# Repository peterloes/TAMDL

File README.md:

# Timed Animal Manipulation Data Logger (TAMDL)
### use timers to trigger your devices

Authors: Loës P., Kempenaers B. (2019) 

Platform for animal observation and manipulation. 

An efficient system to monitor animal behaviour in wildlife
as well as in laboratory settings.

-	Compatible with different RFID systems and triggers
-	Low power consumption and specific data collection lead to long lasting collection periods
-	Applicable world-wide due to its compatibility with different types of radio clock receivers 
-	High observation quality through low disturbance of the animals
- Three user-defined power outputs that can individually be switched on or off at user-defined times

- Time Synchronization with atomic clock once a day to ensure optimal data quality
- Current Control twice a day
- Forecast for Battery-Change implemented
- Energy Bypass so that Date and Time are maintained even when changing battery
- Hyperterminal Output, to get real-time data to the computer/laptop
- Low-Power Device 
- Measure Voltage and Current from your triggered devices 

Picture: Prototype "Activity Logger" with RFID-Reader

https://github.com/peterloes/TAMDL/blob/master/Getting_Started_Tutorial/1_poster_overview_2.pdf

Timed camera trap on nestbox top:

https://github.com/peterloes/TAMDL/blob/master/Getting_Started_Tutorial/1_poster_overview_1.pdf

Raw data on SD Card:

https://github.com/peterloes/TAMDL/blob/master/Getting_Started_Tutorial/6_rawdata_BOX0999.TXT

Configuration data on SD Card:

https://github.com/peterloes/TAMDL/blob/master/Software/CONFIG.TXT

Optional components:

https://github.com/peterloes/Light_Barrier

https://github.com/peterloes/Servo_Engine

https://github.com/peterloes/Linear_Engine

https://github.com/peterloes/Booter_RFID-MS_MOMO_TAMDL

https://github.com/peterloes/Clock_receiver_RFID-MS_MOMO_TAMDL

Manufacture:

https://github.com/peterloes/TAMDL/blob/master/Getting_Started_Tutorial/5_Supplier.txt

C is the Greenest Programming Language

To achieve its power and energy-efficiency features, EFM32 products utilize ultralow active and idle power,
fast wakeup and processing times, and most important, the ability to intelligently interact with peripherals
and sensors autonomously without waking up the CPU and consuming more power.

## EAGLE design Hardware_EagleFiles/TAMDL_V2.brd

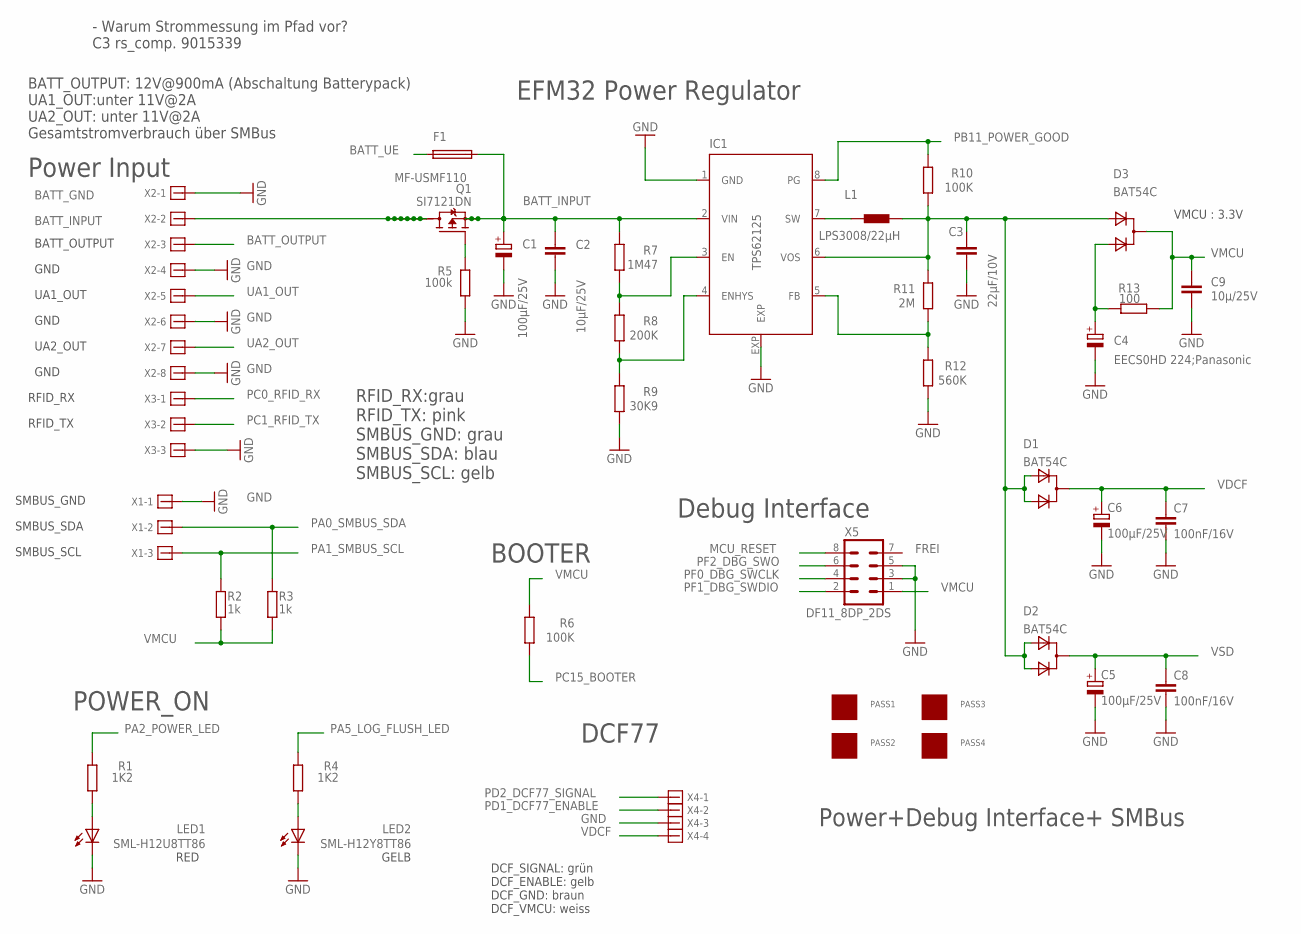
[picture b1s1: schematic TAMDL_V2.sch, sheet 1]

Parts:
C1, C5, C6: 100µF/25V; PANASONIC_E
C2: 10µF/25V; C1206
C3: 22µF/10V; C0603
C4: EECS0HD 224;Panasonic; GOLDCAPSPK-V
C7, C8: 100nF/16V; C0805
C9: 10µ/25V; C1206
D1, D2, D3: BAT54C; SOT-23$1
F1: MF-USMF110; PFUF_1210POLY
IC1: TPS62125; DSG_PWSO-N8_EXP
L1: LPS3008/22µH; LPS3008
LED1: SML-H12U8TT86; CHIPLED_0805
LED2: SML-H12Y8TT86; CHIPLED_0805
PASS1, PASS2, PASS3, PASS4: ROUND_1MM1.5; ROUND2_1.5MM
Q1: SI7121DN; TRANSISTOR-FET_1212-8S
R1, R4: 1K2; R0805
R2, R3: 1k; R0805
R5: 100k; R0805
R6, R10: 100K; R0805
R7: 1M47; R0805
R8: 200K; R0805
R9: 30K9; R0805
R11: 2M; R0805
R12: 560K; R0805
R13: 100; R0805
X1, X3: 1803439
X2: 1803484
X4: 1803442
X5: DF11_8DP_2DS; DP11_8DP-2DS

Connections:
1: C3.1, D1.2 (A1), D1.3 (A2), D2.2 (A1), D2.3 (A2), D3.2 (A1), IC1.6 (VOS), L1.2, R10.1, R11.2
BAT+: Q1.5 (D), Q1.6 (D), Q1.7 (D), Q1.8 (D), Q1.9 (D), Q1.10 (D), Q1.11 (D), X2.2
BATT_INPUT: C1.+, C2.1, F1.P$2 (2), IC1.2 (VIN), Q1.1 (S), Q1.2 (S), Q1.3 (S), R7.2; also elsewhere on the board
BATT_OUTPUT: X2.3; also elsewhere on the board
BATT_UE: F1.P$1 (1); also elsewhere on the board
GND: C1.-, C2.2, C3.2, C4.-, C5.-, C6.-, C7.2, C8.2, C9.1, IC1.1 (GND), IC1.EXP, LED1.C, LED2.C, R5.1, R9.1, R12.1, X1.1, X2.1, X2.4, X2.6, X2.8, X3.3, X4.3, X5.3, X5.5; also elsewhere on the board
MCU_RESET: X5.8; also elsewhere on the board
unnamed: LED1.A, R1.2
unnamed: C4.+, D3.3 (A2), R13.2
unnamed: LED2.A, R4.2
unnamed: IC1.3 (EN), R7.1, R8.2
unnamed: IC1.4 (ENHYS), R8.1, R9.2
unnamed: IC1.7 (SW), L1.1
unnamed: IC1.5 (FB), R11.1, R12.2
unnamed: Q1.4 (G), R5.2
PA0_SMBUS_SDA: R3.2, X1.2; also elsewhere on the board
PA1_SMBUS_SCL: R2.2, X1.3; also elsewhere on the board
PA2_POWER_LED: R1.1; also elsewhere on the board
PA5_LOG_FLUSH_LED: R4.1; also elsewhere on the board
PB11_POWER_GOOD: IC1.8 (PG), R10.2; also elsewhere on the board
PC0_RFID_RX: X3.1; also elsewhere on the board
PC1_RFID_TX: X3.2; also elsewhere on the board
PC15_BOOTER: R6.1; also elsewhere on the board
PD1_DCF77_ENABLE: X4.2; also elsewhere on the board
PD2_DCF77_SIGNAL: X4.1; also elsewhere on the board
PF0_DBG_SWCLK: X5.4; also elsewhere on the board
PF1_DBG_SWDIO: X5.2; also elsewhere on the board
PF2_DBG_SWO: X5.6; also elsewhere on the board
UA1_OUT: X2.5; also elsewhere on the board
UA2_OUT: X2.7; also elsewhere on the board
VDCF: C6.+, C7.1, D1.1 (C), X4.4
VMCU: C9.2, D3.1 (C), R2.1, R3.1, R6.2, R13.1, X5.1; also elsewhere on the board
VSD: C5.+, C8.1, D2.1 (C); also elsewhere on the board

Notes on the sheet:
BATT_GND
BATT_INPUT
BATT_OUTPUT
UA1_OUT
UA2_OUT
GND
RFID_RX
Power+Debug Interface+ SMBus
Power Input
SMBUS_SCL
SMBUS_SDA
SMBUS_GND
EFM32 Power Regulator
Debug Interface
POWER_ON
FREI
VMCU : 3.3V
RED
GELB
BATT_OUTPUT: 12V@900mA (Abschaltung Batterypack) UA1_OUT:unter 11V@2A UA2_OUT: unter 11V@2A Gesamtstromverbrauch über SMBus
RFID_TX
DCF77
RFID_RX:grau RFID_TX: pink SMBUS_GND: grau SMBUS_SDA: blau SMBUS_SCL: gelb
DCF_SIGNAL: grün DCF_ENABLE: gelb DCF_GND: braun DCF_VMCU: weiss
- Warum Strommessung im Pfad vor? C3 rs_comp. 9015339
BOOTER

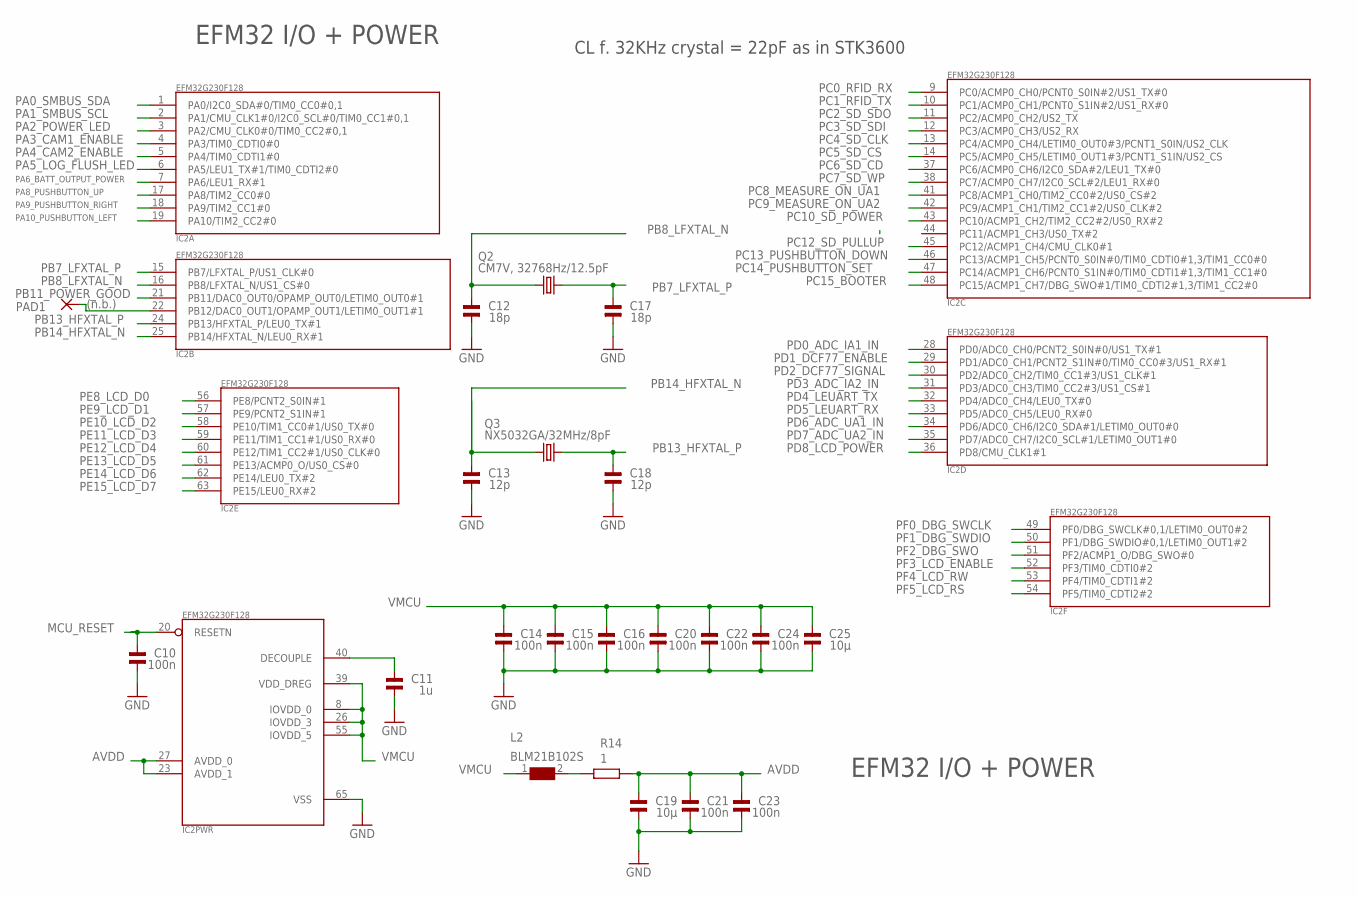
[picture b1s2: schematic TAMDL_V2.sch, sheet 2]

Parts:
C10, C14, C15, C16, C20, C21, C22, C23, C24: 100n; 0805
C11: 1u; 0805
C12, C17: 18p; 0805
C13, C18: 12p; 0805
C19, C25: 10µ; 0805
IC2: EFM32G230F128; QFN64
L2: BLM21B102S; 0805
PAD1: (n.b.); SMD1,27-2,54
Q2: CM7V, 32768Hz/12.5pF; CRYSTAL2P3.2X1.5
Q3: NX5032GA/32MHz/8pF; CRYSTAL2P5.0X3.2
R14: 1; R0805

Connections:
AVDD: C19.2, C21.2, C23.2, IC2.23 (AVDD_1), IC2.27 (AVDD_0), R14.2
GND: C10.1, C11.1, C12.1, C13.1, C14.1, C15.1, C16.1, C17.1, C18.1, C19.1, C20.1, C21.1, C22.1, C23.1, C24.1, C25.1, IC2.65 (VSS); also elsewhere on the board
MCU_RESET: C10.2, IC2.20 (RESETN); also elsewhere on the board
unnamed: L2.2, R14.1
unnamed: IC2.22 (PB12/DAC0_OUT1/OPAMP_OUT1/LETIM0_OUT1#1), PAD1.1
unnamed: C11.2, IC2.40 (DECOUPLE)
PA0_SMBUS_SDA: IC2.1 (PA0/I2C0_SDA#0/TIM0_CC0#0,1); also elsewhere on the board
PA1_SMBUS_SCL: IC2.2 (PA1/CMU_CLK1#0/I2C0_SCL#0/TIM0_CC1#0,1); also elsewhere on the board
PA2_POWER_LED: IC2.3 (PA2/CMU_CLK0#0/TIM0_CC2#0,1); also elsewhere on the board
PA3_CAM1_ENABLE: IC2.4 (PA3/TIM0_CDTI0#0); also elsewhere on the board
PA4_CAM2_ENABLE: IC2.5 (PA4/TIM0_CDTI1#0); also elsewhere on the board
PA5_LOG_FLUSH_LED: IC2.6 (PA5/LEU1_TX#1/TIM0_CDTI2#0); also elsewhere on the board
PA6_BATT_OUTPUT_POWER: IC2.7 (PA6/LEU1_RX#1); also elsewhere on the board
PA8_PUSHBUTTON_UP: IC2.17 (PA8/TIM2_CC0#0); also elsewhere on the board
PA9_PUSHBUTTON_RIGHT: IC2.18 (PA9/TIM2_CC1#0); also elsewhere on the board
PA10_PUSHBUTTON_LEFT: IC2.19 (PA10/TIM2_CC2#0); also elsewhere on the board
PB7_LFXTAL_P: C17.2, IC2.15 (PB7/LFXTAL_P/US1_CLK#0), Q2.2
PB8_LFXTAL_N: C12.2, IC2.16 (PB8/LFXTAL_N/US1_CS#0), Q2.1
PB11_POWER_GOOD: IC2.21 (PB11/DAC0_OUT0/OPAMP_OUT0/LETIM0_OUT0#1); also elsewhere on the board
PB13_HFXTAL_P: C18.2, IC2.24 (PB13/HFXTAL_P/LEU0_TX#1), Q3.2
PB14_HFXTAL_N: C13.2, IC2.25 (PB14/HFXTAL_N/LEU0_RX#1), Q3.1
PC0_RFID_RX: IC2.9 (PC0/ACMP0_CH0/PCNT0_S0IN#2/US1_TX#0); also elsewhere on the board
PC1_RFID_TX: IC2.10 (PC1/ACMP0_CH1/PCNT0_S1IN#2/US1_RX#0); also elsewhere on the board
PC2_SD_SDO: IC2.11 (PC2/ACMP0_CH2/US2_TX); also elsewhere on the board
PC3_SD_SDI: IC2.12 (PC3/ACMP0_CH3/US2_RX); also elsewhere on the board
PC4_SD_CLK: IC2.13 (PC4/ACMP0_CH4/LETIM0_OUT0#3/PCNT1_S0IN/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); also elsewhere on the board
PC5_SD_CS: IC2.14 (PC5/ACMP0_CH5/LETIM0_OUT1#3/PCNT1_S1IN/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); also elsewhere on the board
PC6_SD_CD: IC2.37 (PC6/ACMP0_CH6/I2C0_SDA#2/LEU1_TX#0); also elsewhere on the board
PC7_SD_WP: IC2.38 (PC7/ACMP0_CH7/I2C0_SCL#2/LEU1_RX#0); also elsewhere on the board
PC8_MEASURE_ON_UA1: IC2.41 (PC8/ACMP1_CH0/TIM2_CC0#2/US0_CS#2); also elsewhere on the board
PC9_MEASURE_ON_UA2: IC2.42 (PC9/ACMP1_CH1/TIM2_CC1#2/US0_CLK#2); also elsewhere on the board
PC10_SD_POWER: IC2.43 (PC10/ACMP1_CH2/TIM2_CC2#2/US0_RX#2); also elsewhere on the board
PC12_SD_PULLUP: IC2.45 (PC12/ACMP1_CH4/CMU_CLK0#1); also elsewhere on the board
PC13_PUSHBUTTON_DOWN: IC2.46 (PC13/ACMP1_CH5/PCNT0_S0IN#0/TIM0_CDTI0#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); also elsewhere on the board
PC14_PUSHBUTTON_SET: IC2.47 (PC14/ACMP1_CH6/PCNT0_S1IN#0/TIM0_CDTI1#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); also elsewhere on the board
PC15_BOOTER: IC2.48 (PC15/ACMP1_CH7/DBG_SWO#1/TIM0_CDTI2#1,3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); also elsewhere on the board
PD0_ADC_IA1_IN: IC2.28 (PD0/ADC0_CH0/PCNT2_S0IN#0/US1_TX#1); also elsewhere on the board
PD1_DCF77_ENABLE: IC2.29 (PD1/ADC0_CH1/PCNT2_S1IN#0/TIM0_CC0#3/US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); also elsewhere on the board
PD2_DCF77_SIGNAL: IC2.30 (PD2/ADC0_CH2/TIM0_CC1#3/US1_CLK#1); also elsewhere on the board
PD3_ADC_IA2_IN: IC2.31 (PD3/ADC0_CH3/TIM0_CC2#3/US1_CS#1); also elsewhere on the board
PD4_LEUART_TX: IC2.32 (PD4/ADC0_CH4/LEU0_TX#0); also elsewhere on the board
PD5_LEUART_RX: IC2.33 (PD5/ADC0_CH5/LEU0_RX#0); also elsewhere on the board
PD6_ADC_UA1_IN: IC2.34 (PD6/ADC0_CH6/I2C0_SDA#1/LETIM0_OUT0#0); also elsewhere on the board
PD7_ADC_UA2_IN: IC2.35 (PD7/ADC0_CH7/I2C0_SCL#1/LETIM0_OUT1#0); also elsewhere on the board
PD8_LCD_POWER: IC2.36 (PD8/CMU_CLK1#1); also elsewhere on the board
PE8_LCD_D0: IC2.56 (PE8/PCNT2_S0IN#1); also elsewhere on the board
PE9_LCD_D1: IC2.57 (PE9/PCNT2_S1IN#1); also elsewhere on the board
PE10_LCD_D2: IC2.58 (PE10/TIM1_CC0#1/US0_TX#0); also elsewhere on the board
PE11_LCD_D3: IC2.59 (PE11/TIM1_CC1#1/US0_RX#0); also elsewhere on the board
PE12_LCD_D4: IC2.60 (PE12/TIM1_CC2#1/US0_CLK#0); also elsewhere on the board
PE13_LCD_D5: IC2.61 (PE13/ACMP0_O/US0_CS#0); also elsewhere on the board
PE14_LCD_D6: IC2.62 (PE14/LEU0_TX#2); also elsewhere on the board
PE15_LCD_D7: IC2.63 (PE15/LEU0_RX#2); also elsewhere on the board
PF0_DBG_SWCLK: IC2.49 (PF0/DBG_SWCLK#0,1/LETIM0_OUT0#2); also elsewhere on the board
PF1_DBG_SWDIO: IC2.50 (PF1/DBG_SWDIO#0,1/LETIM0_OUT1#2); also elsewhere on the board
PF2_DBG_SWO: IC2.51 (PF2/ACMP1_O/DBG_SWO#0); also elsewhere on the board
PF3_LCD_ENABLE: IC2.52 (PF3/TIM0_CDTI0#2); also elsewhere on the board
PF4_LCD_RW: IC2.53 (PF4/TIM0_CDTI1#2); also elsewhere on the board
PF5_LCD_RS: IC2.54 (PF5/TIM0_CDTI2#2); also elsewhere on the board
VMCU: C14.2, C15.2, C16.2, C20.2, C22.2, C24.2, C25.2, IC2.8 (IOVDD_0), IC2.26 (IOVDD_3), IC2.39 (VDD_DREG), IC2.55 (IOVDD_5), L2.1; also elsewhere on the board

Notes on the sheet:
EFM32 I/O + POWER
CL f. 32KHz crystal = 22pF as in STK3600

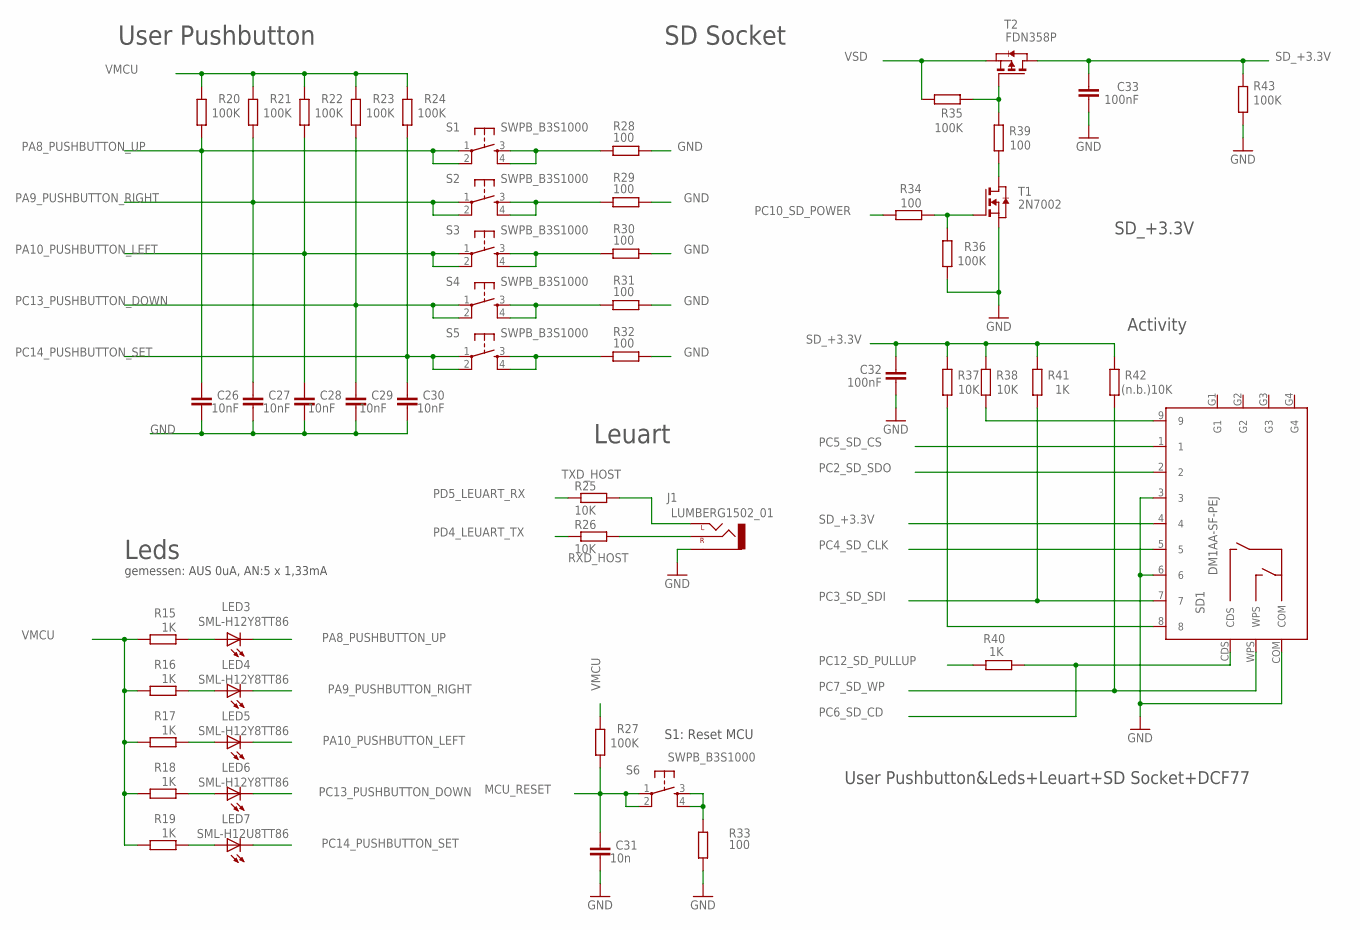
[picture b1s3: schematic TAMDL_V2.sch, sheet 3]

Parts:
C26, C27, C28, C29, C30: 10nF; C0603
C31: 10n; C0603
C32, C33: 100nF; C0603
J1: LUMBERG1502_01
LED3, LED4, LED5, LED6: SML-H12Y8TT86; CHIPLED_0805
LED7: SML-H12U8TT86; CHIPLED_0805
R15, R16, R17, R18, R19, R40, R41: 1K; R0805
R20, R21, R22, R23, R24, R27, R35, R36, R43: 100K; R0805
R25, R26, R37, R38: 10K; R0805
R28, R29, R30, R31, R32, R33, R34, R39: 100; R0805
R42: (n.b.)10K; R0805
S1, S2, S3, S4, S5, S6: SWPB_B3S1000; DTSM-6
SD1: DM1AA-SF-PEJ
T1: 2N7002; ZETEX_SOT-23
T2: FDN358P; ZETEX_SOT-23

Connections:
GND: C26.1, C27.1, C28.1, C29.1, C30.1, C31.1, C32.2, C33.2, J1.P$1 (1-SLEEVE), R28.2, R29.2, R30.2, R31.2, R32.2, R33.2, R36.1, R43.1, SD1.3, SD1.6, SD1.COM, T1.2 (S); also elsewhere on the board
MCU_RESET: C31.2, R27.1, S6.1, S6.2; also elsewhere on the board
unnamed: R33.1, S6.3, S6.4
unnamed: R38.1, SD1.9
unnamed: R37.1, SD1.8
unnamed: LED3.A, R15.1
unnamed: R28.1, S1.3, S1.4
unnamed: R29.1, S2.3, S2.4
unnamed: R30.1, S3.3, S3.4
unnamed: R31.1, S4.3, S4.4
unnamed: R32.1, S5.3, S5.4
unnamed: LED4.A, R16.1
unnamed: R35.1, R39.2, T2.3 (G)
unnamed: R39.1, T1.1 (D)
unnamed: R34.1, R36.2, T1.3 (G)
unnamed: LED5.A, R17.1
unnamed: LED6.A, R18.1
unnamed: LED7.A, R19.1
PA8_PUSHBUTTON_UP: C26.2, LED3.C, R20.1, S1.1, S1.2; also elsewhere on the board
PA9_PUSHBUTTON_RIGHT: C27.2, LED4.C, R21.1, S2.1, S2.2; also elsewhere on the board
PA10_PUSHBUTTON_LEFT: C28.2, LED5.C, R22.1, S3.1, S3.2; also elsewhere on the board
PC2_SD_SDO: SD1.2; also elsewhere on the board
PC3_SD_SDI: R41.1, SD1.7; also elsewhere on the board
PC4_SD_CLK: SD1.5; also elsewhere on the board
PC5_SD_CS: SD1.1; also elsewhere on the board
PC6_SD_CD: R40.2, SD1.CDS; also elsewhere on the board
PC7_SD_WP: R42.1, SD1.WPS; also elsewhere on the board
PC10_SD_POWER: R34.2; also elsewhere on the board
PC12_SD_PULLUP: R40.1; also elsewhere on the board
PC13_PUSHBUTTON_DOWN: C29.2, LED6.C, R23.1, S4.1, S4.2; also elsewhere on the board
PC14_PUSHBUTTON_SET: C30.2, LED7.C, R24.1, S5.1, S5.2; also elsewhere on the board
PD4_LEUART_TX: R26.1; also elsewhere on the board
PD5_LEUART_RX: R25.1; also elsewhere on the board
RXD_HOST: J1.P$3 (3-RIGHT), R26.2
SD_+3.3V: C32.1, C33.1, R37.2, R38.2, R41.2, R42.2, R43.2, SD1.4, T2.1 (D)
TXD_HOST: J1.P$2 (2-LEFT), R25.2
VMCU: R15.2, R16.2, R17.2, R18.2, R19.2, R20.2, R21.2, R22.2, R23.2, R24.2, R27.2; also elsewhere on the board
VSD: R35.2, T2.2 (S); also elsewhere on the board

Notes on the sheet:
gemessen: AUS 0uA, AN:5 x 1,33mA
User Pushbutton&Leds+Leuart+SD Socket+DCF77
User Pushbutton
Leds
Leuart
SD Socket
SD_+3.3V
Activity
S1: Reset MCU

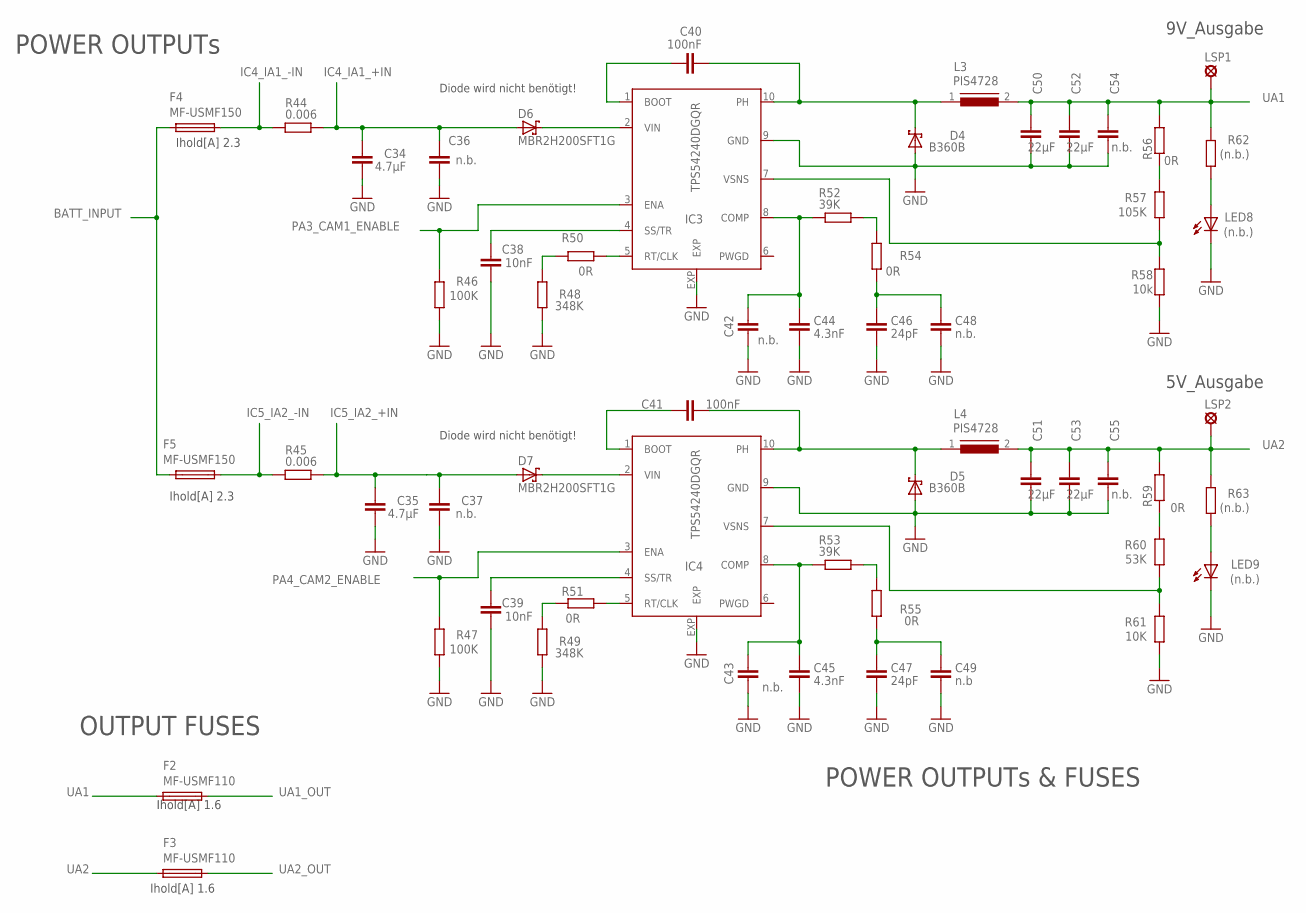
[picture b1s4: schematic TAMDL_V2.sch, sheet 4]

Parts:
C34, C35: 4.7µF; C1210
C36, C37, C54, C55: n.b.; C1210
C38, C39: 10nF; C0603
C40, C41: 100nF; C0603
C42, C43, C48: n.b.; C0603
C44, C45: 4.3nF; C0603
C46, C47: 24pF; C0603
C49: n.b; C0603
C50, C51, C52, C53: 22µF; C1210
D4, D5: B360B; SMB
D6, D7: MBR2H200SFT1G; SOD123FL
F2, F3: MF-USMF110; PFUF_1210POLY
F4, F5: MF-USMF150; PFUF_1210POLY
IC3, IC4: TPS54240DGQR; S-PDSO-G10
L3, L4: PIS4728; DR127
LED8, LED9: (n.b.); CHIPLED_0805
LSP1, LSP2: (n.b.)SE13; SE13
R44, R45: 0.006; R2512W
R46, R47: 100K; R0805
R48, R49: 348K; R0805
R50, R51, R54, R55, R56, R59: 0R; R0805
R52, R53: 39K; R0805
R57: 105K; R0805
R58: 10k; R0805
R60: 53K; R0805
R61: 10K; R0805
R62, R63: (n.b.); R0805

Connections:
BATT_INPUT: F4.P$1 (1), F5.P$1 (1); also elsewhere on the board
GND: C34.2, C35.2, C36.2, C37.2, C38.2, C39.2, C42.2, C43.2, C44.2, C45.2, C46.2, C47.2, C48.2, C49.2, C50.2, C51.2, C52.2, C53.2, C54.2, C55.2, D4.A, D5.A, IC3.9 (GND), IC3.EXP, IC4.9 (GND), IC4.EXP, LED8.C, LED9.C, R46.1, R47.1, R48.1, R49.1, R58.1, R61.1; also elsewhere on the board
IC4_IA1_+IN: C34.1, C36.1, D6.A, R44.2; also elsewhere on the board
IC4_IA1_-IN: F4.P$2 (2), R44.1; also elsewhere on the board
IC5_IA2_+IN: C35.1, C37.1, D7.A, R45.2; also elsewhere on the board
IC5_IA2_-IN: F5.P$2 (2), R45.1; also elsewhere on the board
unnamed: C40.2, IC3.1 (BOOT)
unnamed: C40.1, D4.C, IC3.10 (PH), L3.1
unnamed: C38.1, IC3.4 (SS/TR)
unnamed: C42.1, C44.1, IC3.8 (COMP), R52.1
unnamed: C46.1, C48.1, R54.1
unnamed: IC3.7 (VSNS), R57.1, R58.2
unnamed: C41.2, IC4.1 (BOOT)
unnamed: C41.1, D5.C, IC4.10 (PH), L4.1
unnamed: C39.1, IC4.4 (SS/TR)
unnamed: C43.1, C45.1, IC4.8 (COMP), R53.1
unnamed: C47.1, C49.1, R55.1
unnamed: IC4.7 (VSNS), R60.1, R61.2
unnamed: LED9.A, R63.1
unnamed: R48.2, R50.1
unnamed: D6.C, IC3.2 (VIN)
unnamed: R49.2, R51.1
unnamed: IC3.5 (RT/CLK), R50.2
unnamed: R52.2, R54.2
unnamed: R56.1, R57.2
unnamed: IC4.5 (RT/CLK), R51.2
unnamed: R59.1, R60.2
unnamed: R53.2, R55.2
unnamed: D7.C, IC4.2 (VIN)
unnamed: LED8.A, R62.1
PA3_CAM1_ENABLE: IC3.3 (ENA), R46.2; also elsewhere on the board
PA4_CAM2_ENABLE: IC4.3 (ENA), R47.2; also elsewhere on the board
UA1: C50.1, C52.1, C54.1, F2.P$1 (1), L3.2, LSP1.MP, R56.2, R62.2; also elsewhere on the board
UA1_OUT: F2.P$2 (2); also elsewhere on the board
UA2: C51.1, C53.1, C55.1, F3.P$1 (1), L4.2, LSP2.MP, R59.2, R63.2; also elsewhere on the board
UA2_OUT: F3.P$2 (2); also elsewhere on the board

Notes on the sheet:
9V_Ausgabe
5V_Ausgabe
POWER OUTPUTs & FUSES
POWER OUTPUTs
OUTPUT FUSES
Ihold[A] 2.3
Ihold[A] 1.6
Diode wird nicht benötigt!

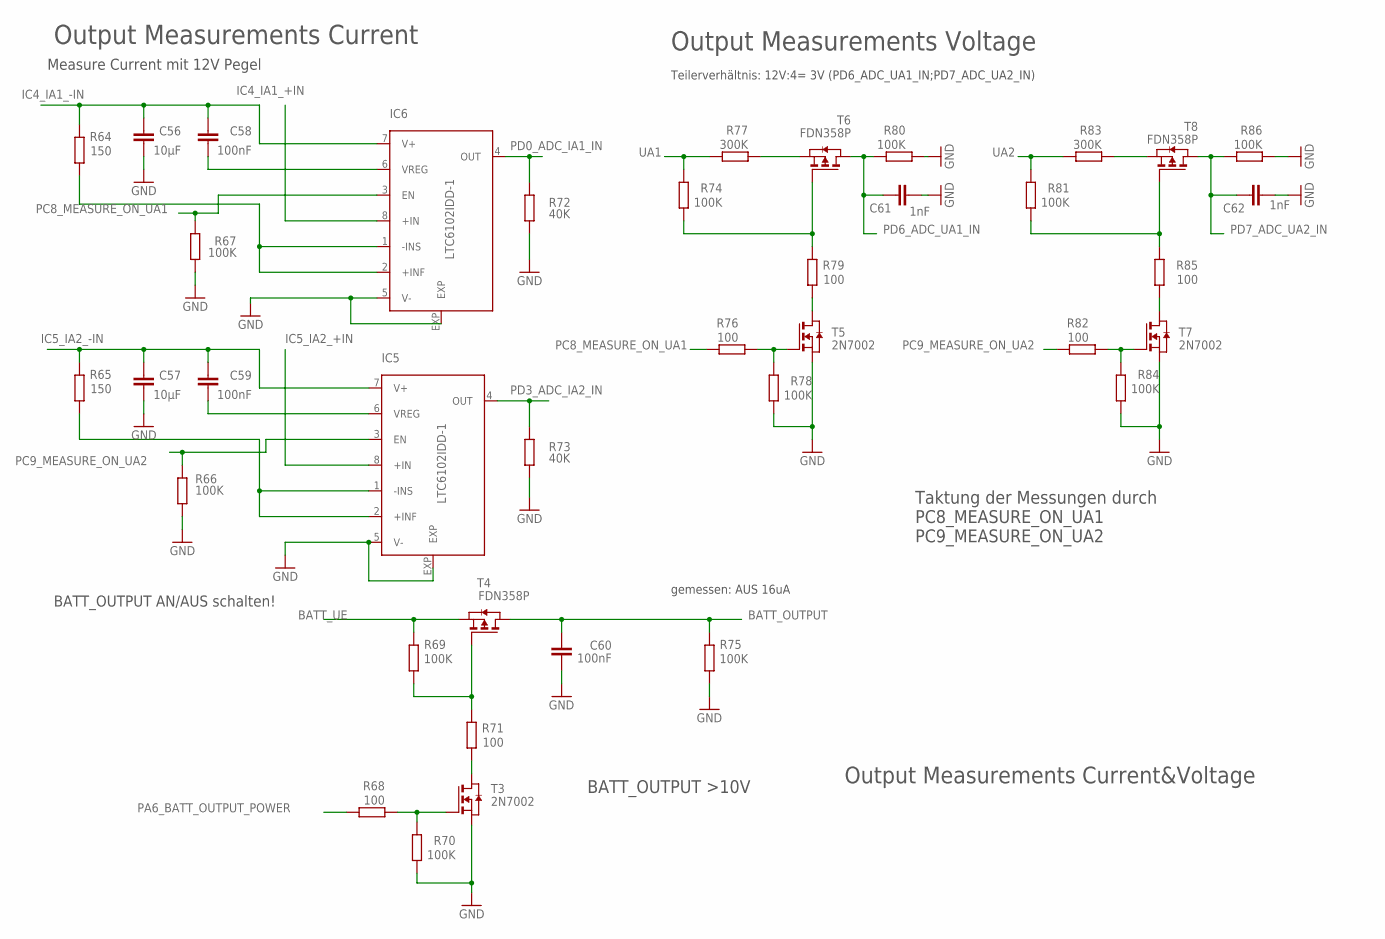
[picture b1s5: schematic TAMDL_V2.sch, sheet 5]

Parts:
C56, C57: 10µF; C1206
C58, C59, C60: 100nF; C0603
C61, C62: 1nF; C0603
IC5, IC6: LTC6102IDD-1; DFN8-LEAD
R64, R65: 150; R0805
R66, R67, R69, R70, R74, R75, R78, R80, R81, R84, R86: 100K; R0805
R68, R71, R76, R79, R82, R85: 100; R0805
R72, R73: 40K; R0805
R77, R83: 300K; R0805
T3, T5, T7: 2N7002; ZETEX_SOT-23
T4, T6, T8: FDN358P; ZETEX_SOT-23

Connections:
BATT_OUTPUT: C60.1, R75.2, T4.1 (D); also elsewhere on the board
BATT_UE: R69.2, T4.2 (S); also elsewhere on the board
GND: C56.1, C57.1, C60.2, C61.2, C62.2, IC5.5 (V-), IC5.EXP, IC6.5 (V-), IC6.EXP, R66.2, R67.2, R70.1, R72.2, R73.2, R75.1, R78.1, R80.1, R84.1, R86.1, T3.2 (S), T5.2 (S), T7.2 (S); also elsewhere on the board
IC4_IA1_+IN: IC6.8 (+IN); also elsewhere on the board
IC4_IA1_-IN: C56.2, C58.2, IC6.7 (V+), R64.2; also elsewhere on the board
IC5_IA2_+IN: IC5.8 (+IN); also elsewhere on the board
IC5_IA2_-IN: C57.2, C59.2, IC5.7 (V+), R65.2; also elsewhere on the board
unnamed: R69.1, R71.2, T4.3 (G)
unnamed: R71.1, T3.1 (D)
unnamed: R68.1, R70.2, T3.3 (G)
unnamed: R74.1, R79.2, T6.3 (G)
unnamed: IC6.1 (-INS), IC6.2 (+INF), R64.1
unnamed: C58.1, IC6.6 (VREG)
unnamed: IC5.1 (-INS), IC5.2 (+INF), R65.1
unnamed: C59.1, IC5.6 (VREG)
unnamed: R79.1, T5.1 (D)
unnamed: R76.1, R78.2, T5.3 (G)
unnamed: R81.1, R85.2, T8.3 (G)
unnamed: R85.1, T7.1 (D)
unnamed: R82.1, R84.2, T7.3 (G)
unnamed: R77.1, T6.2 (S)
unnamed: R83.1, T8.2 (S)
PA6_BATT_OUTPUT_POWER: R68.2; also elsewhere on the board
PC8_MEASURE_ON_UA1: IC6.3 (EN), R67.1, R76.2; also elsewhere on the board
PC9_MEASURE_ON_UA2: IC5.3 (EN), R66.1, R82.2; also elsewhere on the board
PD0_ADC_IA1_IN: IC6.4 (OUT), R72.1; also elsewhere on the board
PD3_ADC_IA2_IN: IC5.4 (OUT), R73.1; also elsewhere on the board
PD6_ADC_UA1_IN: C61.1, R80.2, T6.1 (D); also elsewhere on the board
PD7_ADC_UA2_IN: C62.1, R86.2, T8.1 (D); also elsewhere on the board
UA1: R74.2, R77.2; also elsewhere on the board
UA2: R81.2, R83.2; also elsewhere on the board

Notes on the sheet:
Measure Current mit 12V Pegel
Output Measurements Current&Voltage
Output Measurements Current
Output Measurements Voltage
gemessen: AUS 16uA
BATT_OUTPUT >10V
BATT_OUTPUT AN/AUS schalten!
Taktung der Messungen durch PC8_MEASURE_ON_UA1 PC9_MEASURE_ON_UA2
Teilerverhältnis: 12V:4= 3V (PD6_ADC_UA1_IN;PD7_ADC_UA2_IN)

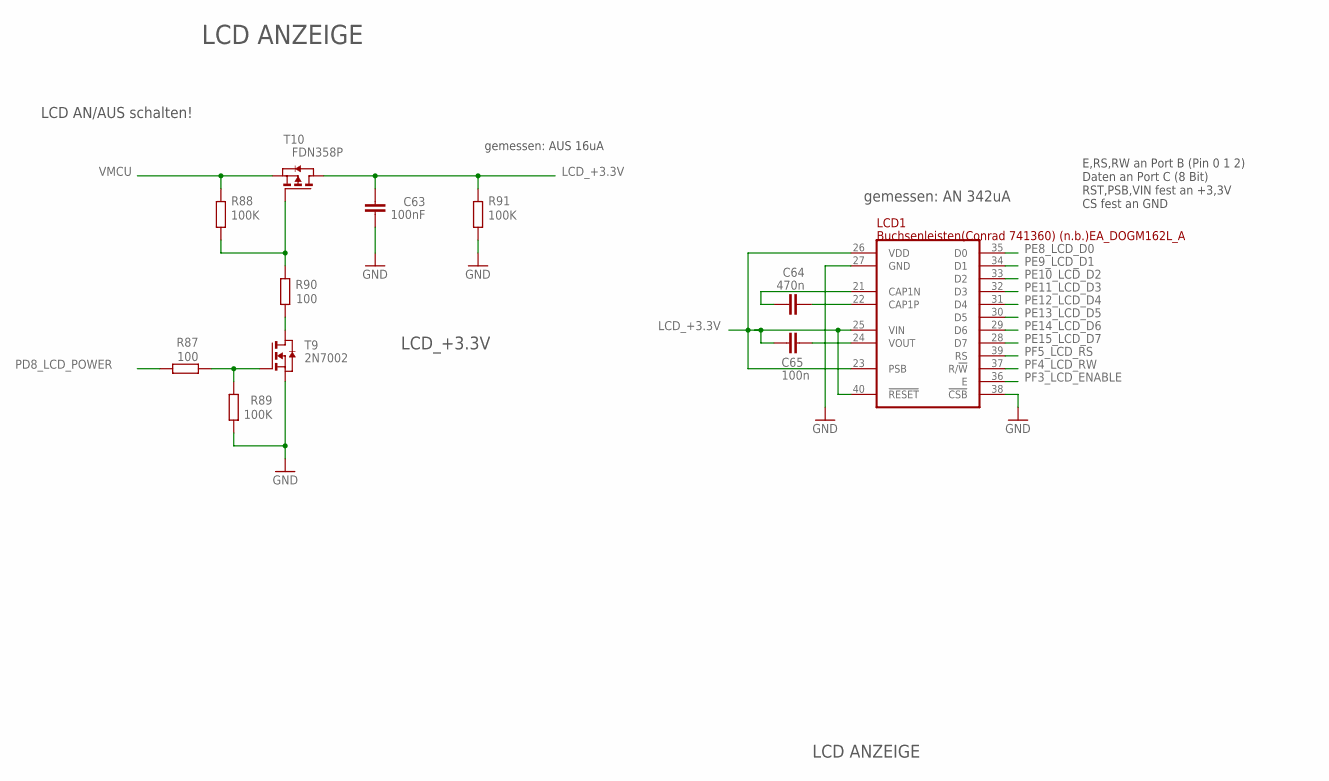
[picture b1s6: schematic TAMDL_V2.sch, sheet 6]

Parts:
C63: 100nF; C0603
C64: 470n; C0805
C65: 100n; C1206
LCD1: Buchsenleisten(Conrad 741360) (n.b.)EA_DOGM162L_A; EA_DOGM
R87, R90: 100; R0805
R88, R89, R91: 100K; R0805
T9: 2N7002; ZETEX_SOT-23
T10: FDN358P; ZETEX_SOT-23

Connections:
GND: C63.2, LCD1.27 (GND), LCD1.38 (!CSB!), R89.1, R91.1, T9.2 (S); also elsewhere on the board
LCD_+3.3V: C63.1, C65.2, LCD1.23 (PSB), LCD1.25 (VIN), LCD1.26 (VDD), LCD1.40 (!RESET!), R91.2, T10.1 (D)
unnamed: R88.1, R90.2, T10.3 (G)
unnamed: R90.1, T9.1 (D)
unnamed: R87.1, R89.2, T9.3 (G)
unnamed: C64.1, LCD1.21 (CAP1N)
unnamed: C64.2, LCD1.22 (CAP1P)
unnamed: C65.1, LCD1.24 (VOUT)
PD8_LCD_POWER: R87.2; also elsewhere on the board
PE8_LCD_D0: LCD1.35 (D0); also elsewhere on the board
PE9_LCD_D1: LCD1.34 (D1); also elsewhere on the board
PE10_LCD_D2: LCD1.33 (D2); also elsewhere on the board
PE11_LCD_D3: LCD1.32 (D3); also elsewhere on the board
PE12_LCD_D4: LCD1.31 (D4); also elsewhere on the board
PE13_LCD_D5: LCD1.30 (D5); also elsewhere on the board
PE14_LCD_D6: LCD1.29 (D6); also elsewhere on the board
PE15_LCD_D7: LCD1.28 (D7); also elsewhere on the board
PF3_LCD_ENABLE: LCD1.36 (E); also elsewhere on the board
PF4_LCD_RW: LCD1.37 (R/!W!); also elsewhere on the board
PF5_LCD_RS: LCD1.39 (RS); also elsewhere on the board
VMCU: R88.2, T10.2 (S); also elsewhere on the board

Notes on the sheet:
LCD ANZEIGE
E,RS,RW an Port B (Pin 0 1 2) Daten an Port C (8 Bit) RST,PSB,VIN fest an +3,3V CS fest an GND
gemessen: AUS 16uA
LCD_+3.3V
LCD AN/AUS schalten!
gemessen: AN 342uA

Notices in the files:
parts and their libraries:
EnergyMicro: CC0 License
SparkFun-Aesthetics: Licensing: CC v3.0 Share-Alike You are welcome to use this library for commercial purposes.
